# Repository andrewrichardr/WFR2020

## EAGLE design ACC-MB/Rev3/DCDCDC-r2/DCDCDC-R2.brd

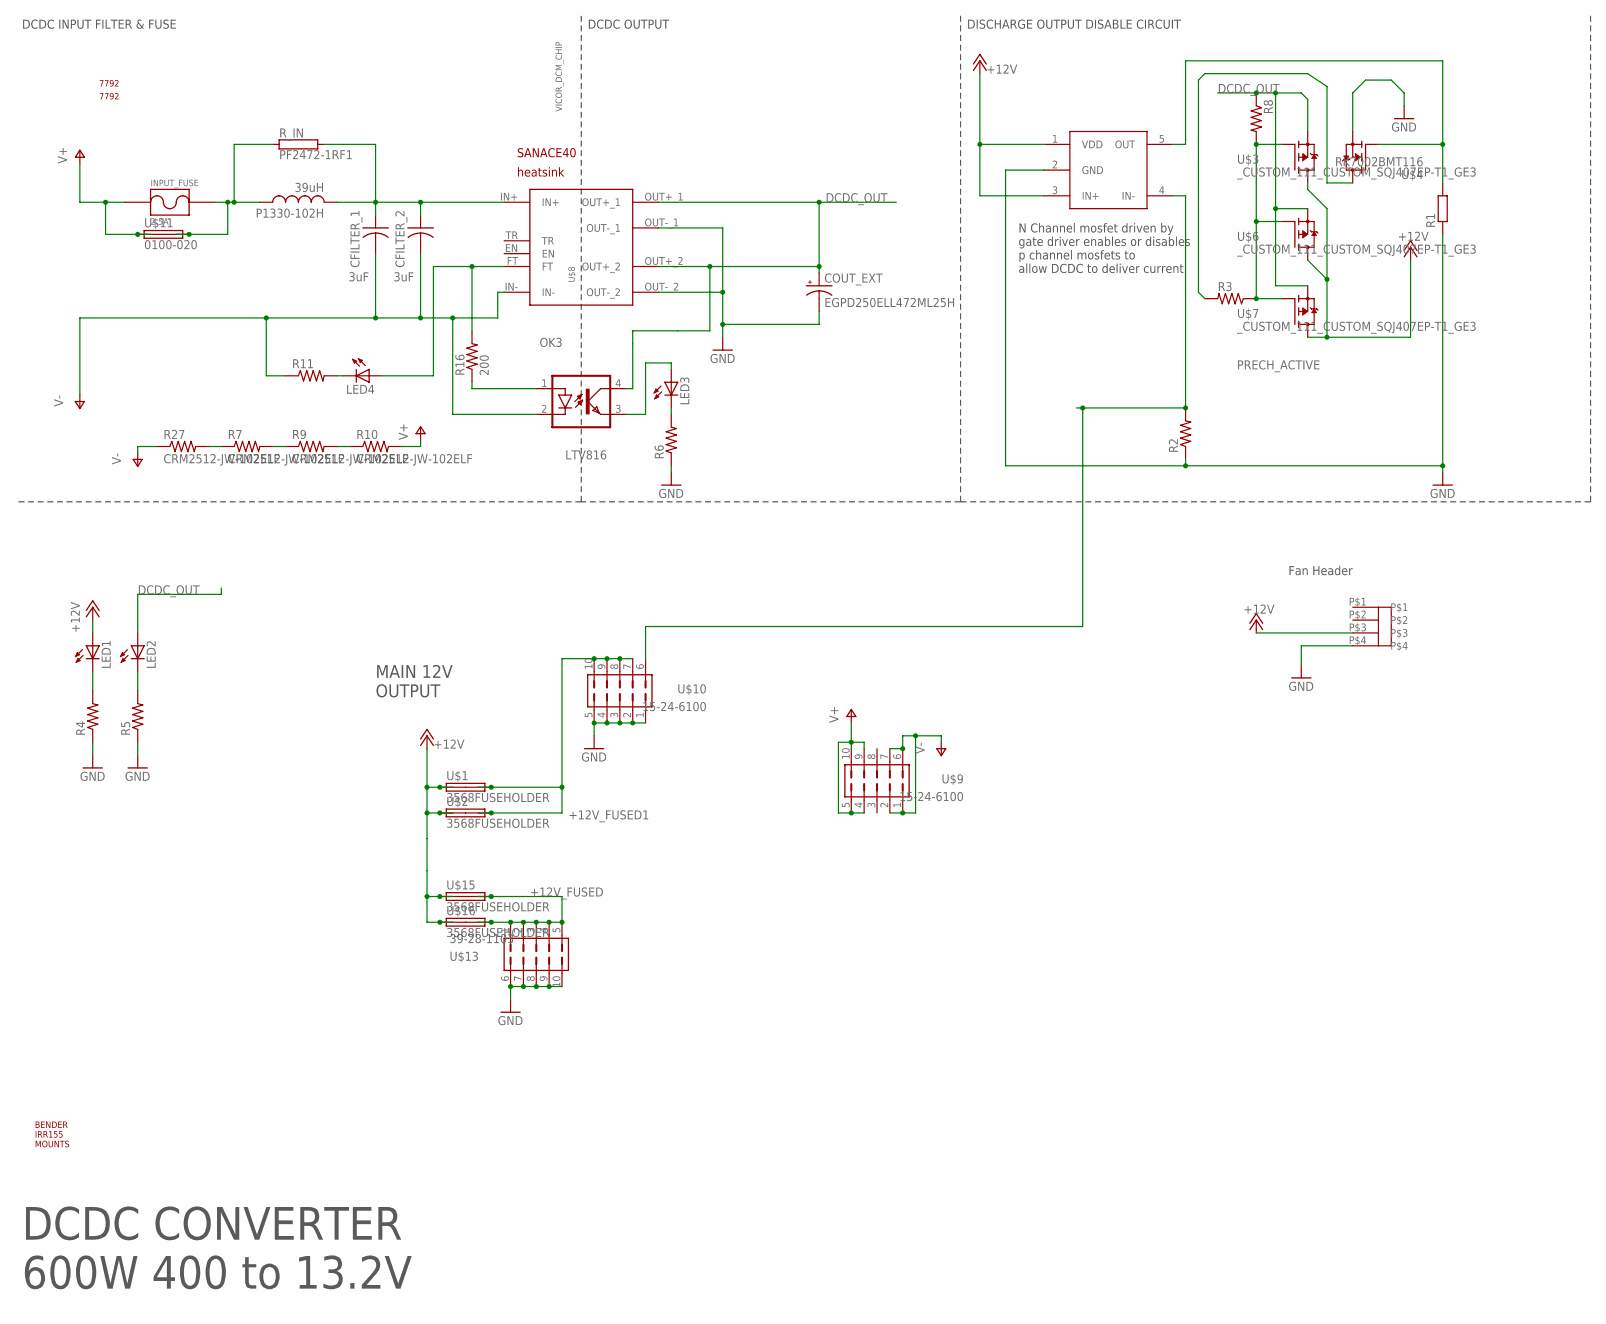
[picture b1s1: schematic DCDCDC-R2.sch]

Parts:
CFILTER_1, CFILTER_2: 3uF; CERALINK_FA3
COUT_EXT: EGPD250ELL472ML25H; E7,5-16
INPUT_FUSE: 2.5A; _CUSTOM_PARTS_LF_885
LED1, LED2, LED3, LED4: LEDCHIPLED_0805; CHIPLED_0805
OK3: LTV816; DIL04
P1330-102H: 39uH; L_1510_NONSTANDARD
R1: R-EU_R0805; R0805
R2, R3, R4, R5, R6, R8, R11: R-US_R0805; R0805
R7, R9, R10, R27: CRM2512-JW-102ELF; R2512
R16: 200; R2010
R_IN: PF2472-1RF1; TO-247-2V
U$1, U$2, U$15, U$16: 3568FUSEHOLDER; 3568
U$3, U$6, U$7: _CUSTOM_111_CUSTOM_SQJ407EP-T1_GE3; _CUSTOM_111_CUSTOM_TRANS_SIRA90DP-T1-GE3
U$4: RK7002BMT116; SOT23
U$5: UCC27511AQDBVRQ1; SOT23-5L
U$8: VICOR_DCM_CHIP; VICOR_CHIP_HEATSINK
U$9, U$10: 15-24-6100
U$11: 0100-020
U$12: VICOR_HEATSINK_DOUBLE
U$13: 39-28-1103
U$14, U$17: 7792
U$18: 9GAX0412P3S0031; SANACE40
U$19: 470531000
U$20: BENDER_IRR155

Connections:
+12V: LED1.A, U$1.L1 (1A), U$1.L2 (1B), U$2.L1 (1A), U$2.L2 (1B), U$3.5 (D), U$5.1 (VDD), U$5.3 (IN+), U$6.5 (D), U$7.5 (D), U$15.L1 (1A), U$15.L2 (1B), U$16.L1 (1A), U$16.L2 (1B), U$19.P$3
+12V_FUSED: U$13.1, U$13.2, U$13.3, U$13.4, U$13.5, U$15.R1 (2A), U$15.R2 (2B), U$16.R1 (2A), U$16.R2 (2B)
+12V_FUSED1: U$1.R1 (2A), U$1.R2 (2B), U$2.R1 (2A), U$2.R2 (2B), U$10.7, U$10.8, U$10.9, U$10.10
DCDC_OUT: COUT_EXT.+, LED2.A, OK3.4 (COL), R8.1, U$3.1 (S), U$3.2 (S), U$3.3 (S), U$6.1 (S), U$6.2 (S), U$6.3 (S), U$7.1 (S), U$7.2 (S), U$7.3 (S), U$8.OUT+_1, U$8.OUT+_2
GND: COUT_EXT.-, R1.1, R2.1, R4.1, R5.1, R6.1, U$4.2 (S), U$5.2 (GND), U$8.OUT-_1, U$8.OUT-_2, U$10.1, U$10.2, U$10.3, U$10.4, U$10.5, U$13.6, U$13.7, U$13.8, U$13.9, U$13.10, U$19.P$4
unnamed: R3.1, R8.2, U$3.4 (G), U$6.4 (G), U$7.4 (G)
unnamed: R1.2, U$4.1 (G), U$5.5 (OUT)
unnamed: CFILTER_1.P$1 (1), CFILTER_2.P$1 (1), P1330-102H.P$2 (2), R_IN.2, U$8.IN+
unnamed: R3.2, U$4.3 (D)
unnamed: LED1.C, R4.2
unnamed: LED2.C, R5.2
unnamed: LED4.A, R16.2, U$8.FT
unnamed: OK3.1 (A), R16.1
unnamed: LED3.C, R6.2
unnamed: LED3.A, OK3.3 (EMIT)
unnamed: LED4.C, R11.2
unnamed: R7.1, R27.2
unnamed: R7.2, R9.1
unnamed: R9.2, R10.1
PRECH_ACTIVE: R2.2, U$5.4 (IN-), U$10.6
V+: INPUT_FUSE.P$1, R10.2, U$9.4, U$9.5, U$9.9, U$9.10, U$11.P$1 (1A), U$11.P$3 (1B)
V+_FUSED: INPUT_FUSE.P$2, P1330-102H.P$1 (1), R_IN.1, U$11.P$2 (2A), U$11.P$4 (2B)
V-: CFILTER_1.P$2 (2), CFILTER_2.P$2 (2), OK3.2 (C), R11.1, R27.1, U$8.IN-, U$9.1, U$9.2, U$9.6, U$9.7

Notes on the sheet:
DCDC CONVERTER 600W 400 to 13.2V
DISCHARGE OUTPUT DISABLE CIRCUIT
Fan Header
MAIN 12V OUTPUT
DCDC OUTPUT
DCDC INPUT FILTER & FUSE
N Channel mosfet driven by gate driver enables or disables p channel mosfets to allow DCDC to deliver current

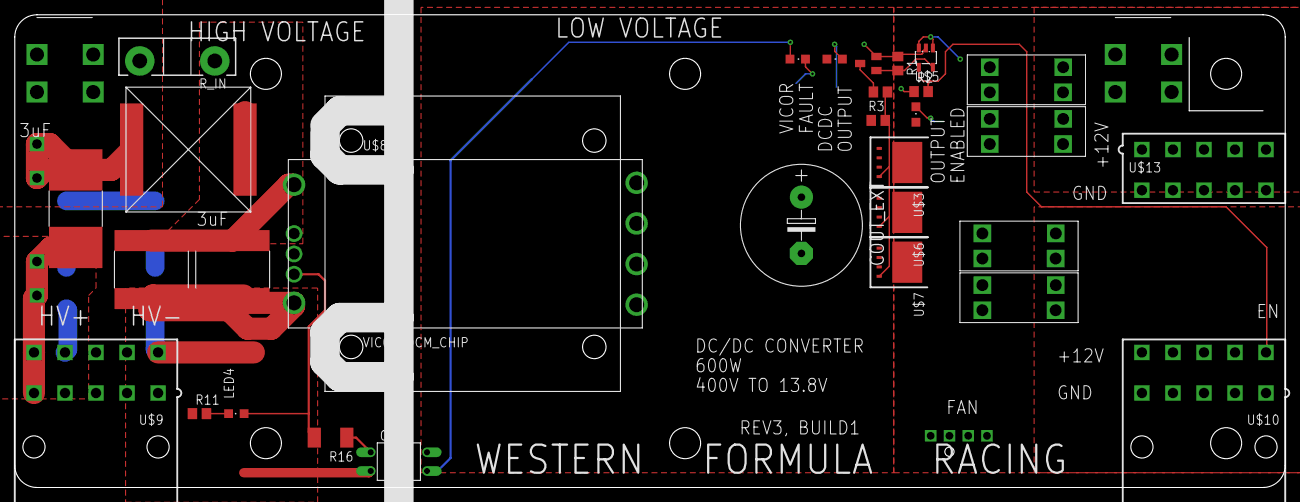
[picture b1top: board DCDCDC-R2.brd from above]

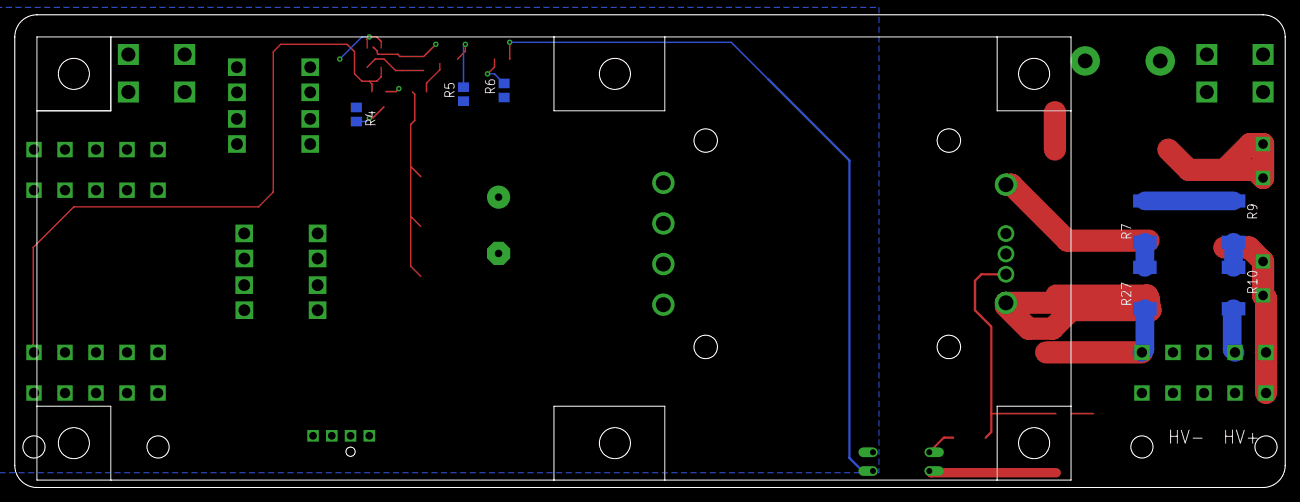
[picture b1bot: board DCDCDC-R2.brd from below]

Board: 2 copper layers, 172.0 x 64.0 mm, 44 parts (8 on the bottom side), 23 nets.

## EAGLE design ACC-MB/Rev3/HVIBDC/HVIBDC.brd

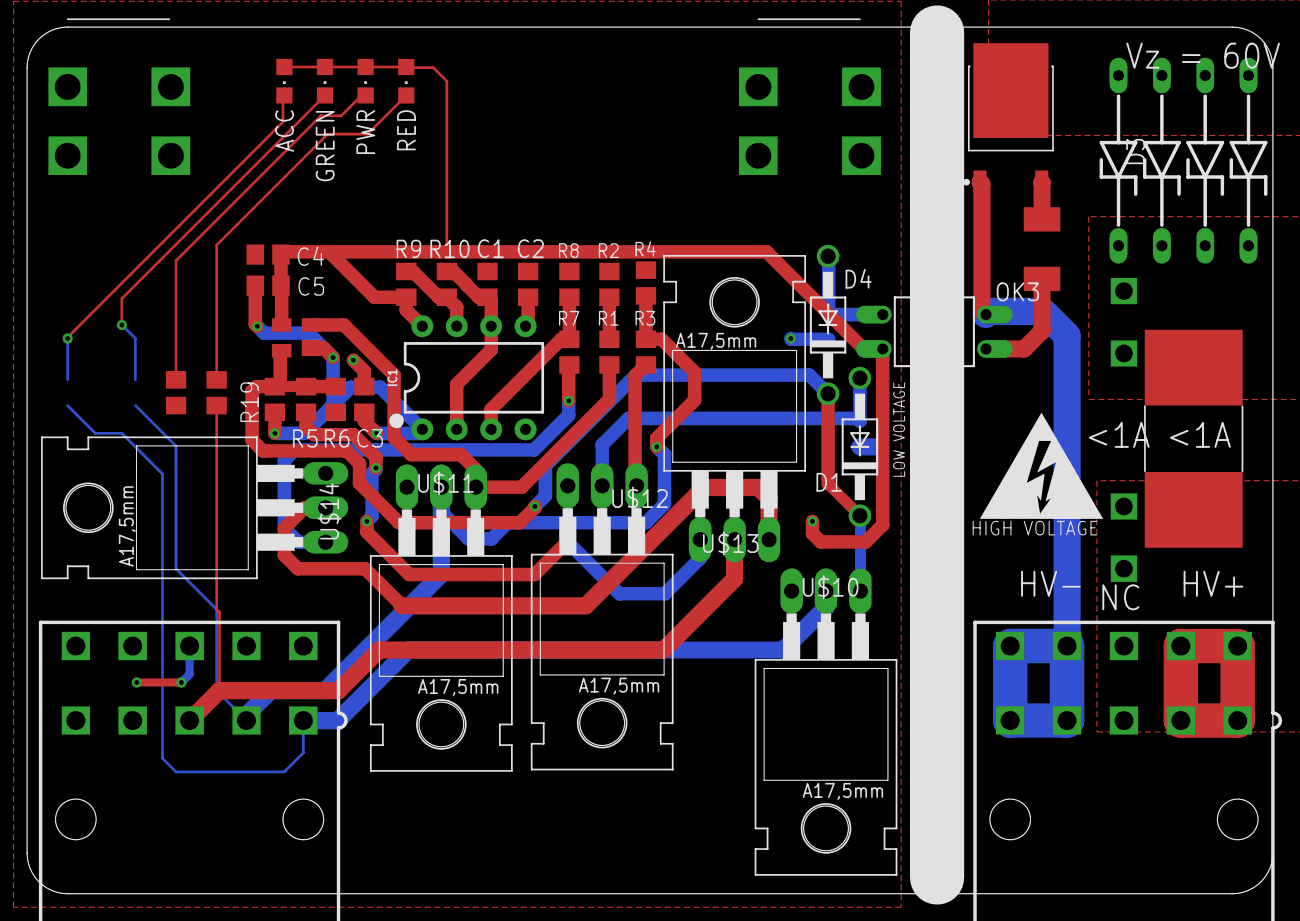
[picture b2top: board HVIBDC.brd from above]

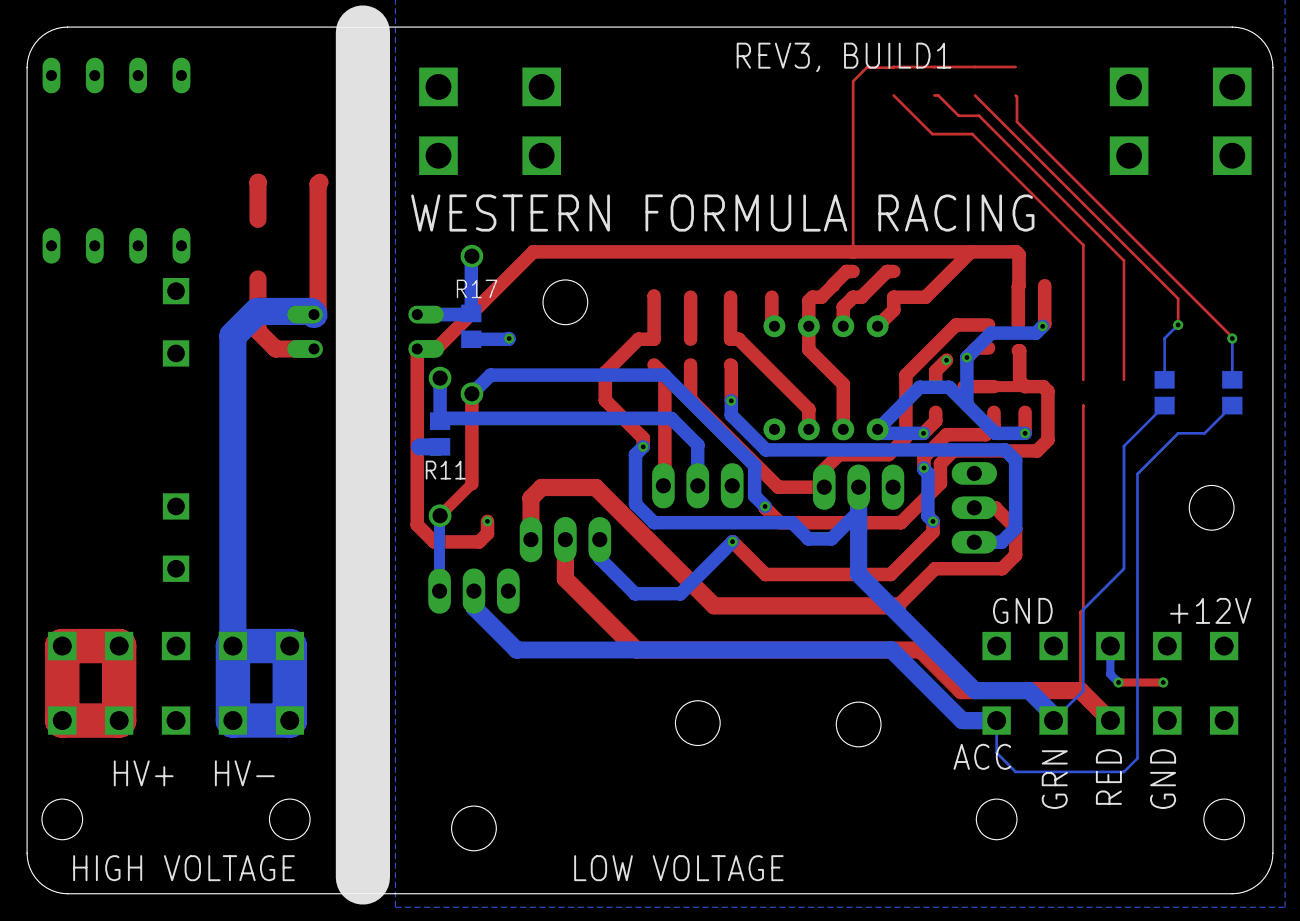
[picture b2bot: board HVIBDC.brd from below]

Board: 2 copper layers, 92.0 x 64.0 mm, 48 parts (4 on the bottom side), 28 nets.

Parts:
ACC: CHIPLED_0805
C1: 39n; C0805
C2: 10n; C0805
C3: 100n; C0805
C4: 4.7u; C0805
C5: 0.1u; C0805
D1, D4: 1N4004; DO41-10
D2, D3, D5, D6: 1N4758A - 56Vz; ZDIO12.5
GREEN: CHIPLED_0805
HV+_FUSE_DRY: _CUSTOM_PARTS_LF_885
IC1: 555; DIP08
LEDR1, LEDR2, LEDR3, LEDR4: R0805
OK3: LTV816; DIL04
PWR: CHIPLED_0805
R1, R3, R5, R7: 100; R0805
R2, R4, R6, R8, R11: 1M; R0805
R9: 2.2k; R0805
R10: 4.7M; R0805
R16: 200; R2010
R17, R19: 10k; R0805
RED: CHIPLED_0805
U$1, U$2: 15-24-6100
U$3, U$4: 7792
U$8: 0100-020
U$10, U$11, U$12, U$13, U$14: BUZ11; TO220
U$15: MIC4417; PDM_2019_REVB_MIC4416YM4-TR
U$22: _CUSTOM_IXCY10M90SD2PAK; TO228P991X238-3

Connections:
+12V: ACC.A, C3.1, C4.1, C5.1, GREEN.A, IC1.4, IC1.8, OK3.4, PWR.A, R9.2, R11.2, RED.A, U$2.8, U$2.9, U$2.10, U$15.VS
ACC_LGHT: LEDR3.1, U$2.1, U$10.2
AIR_ON: D1.C, D4.C, R5.1, R6.2, R19.2, U$10.1, U$15.CTL
GND: C1.2, C2.2, C3.2, C4.2, C5.2, IC1.1, LEDR4.1, R2.1, R4.1, R6.1, R8.1, R17.1, R19.1, U$2.4, U$2.5, U$2.6, U$2.7, U$10.3, U$11.3, U$12.3, U$14.3, U$15.GND
HV+_DRY_FUSED: D2.C, D3.C, D5.C, D6.C, HV+_FUSE_DRY.P$1, U$8.P$2, U$8.P$4
unnamed: R1.1, R2.2
unnamed: R1.2, U$11.1, U$15.GATE
unnamed: R3.2, U$12.1
unnamed: C2.1, IC1.5
unnamed: IC1.7, R9.1, R10.2
unnamed: R5.2, U$13.1
unnamed: R7.2, U$14.1
unnamed: IC1.3, R7.1, R8.2
unnamed: C1.1, IC1.2, IC1.6, R10.1
unnamed: ACC.C, LEDR3.2
unnamed: GREEN.C, LEDR1.2
unnamed: U$13.3, U$14.2
unnamed: D4.A, OK3.3, R17.2
unnamed: D1.A, R11.1, U$12.2
unnamed: LEDR2.2, RED.C
unnamed: LEDR4.2, PWR.C
unnamed: R16.2, U$22.2
unnamed: D2.A, D3.A, D5.A, D6.A, U$22.3
unnamed: OK3.1, R16.1
TSAL_GRN_GND: LEDR1.1, R3.1, R4.2, U$2.2, U$11.2
TSAL_RED_GND: LEDR2.1, U$2.3, U$13.2
V+: HV+_FUSE_DRY.P$2, U$1.1, U$1.2, U$1.6, U$1.7, U$8.P$1, U$8.P$3
V-: OK3.2, U$1.4, U$1.5, U$1.9, U$1.10, U$22.1

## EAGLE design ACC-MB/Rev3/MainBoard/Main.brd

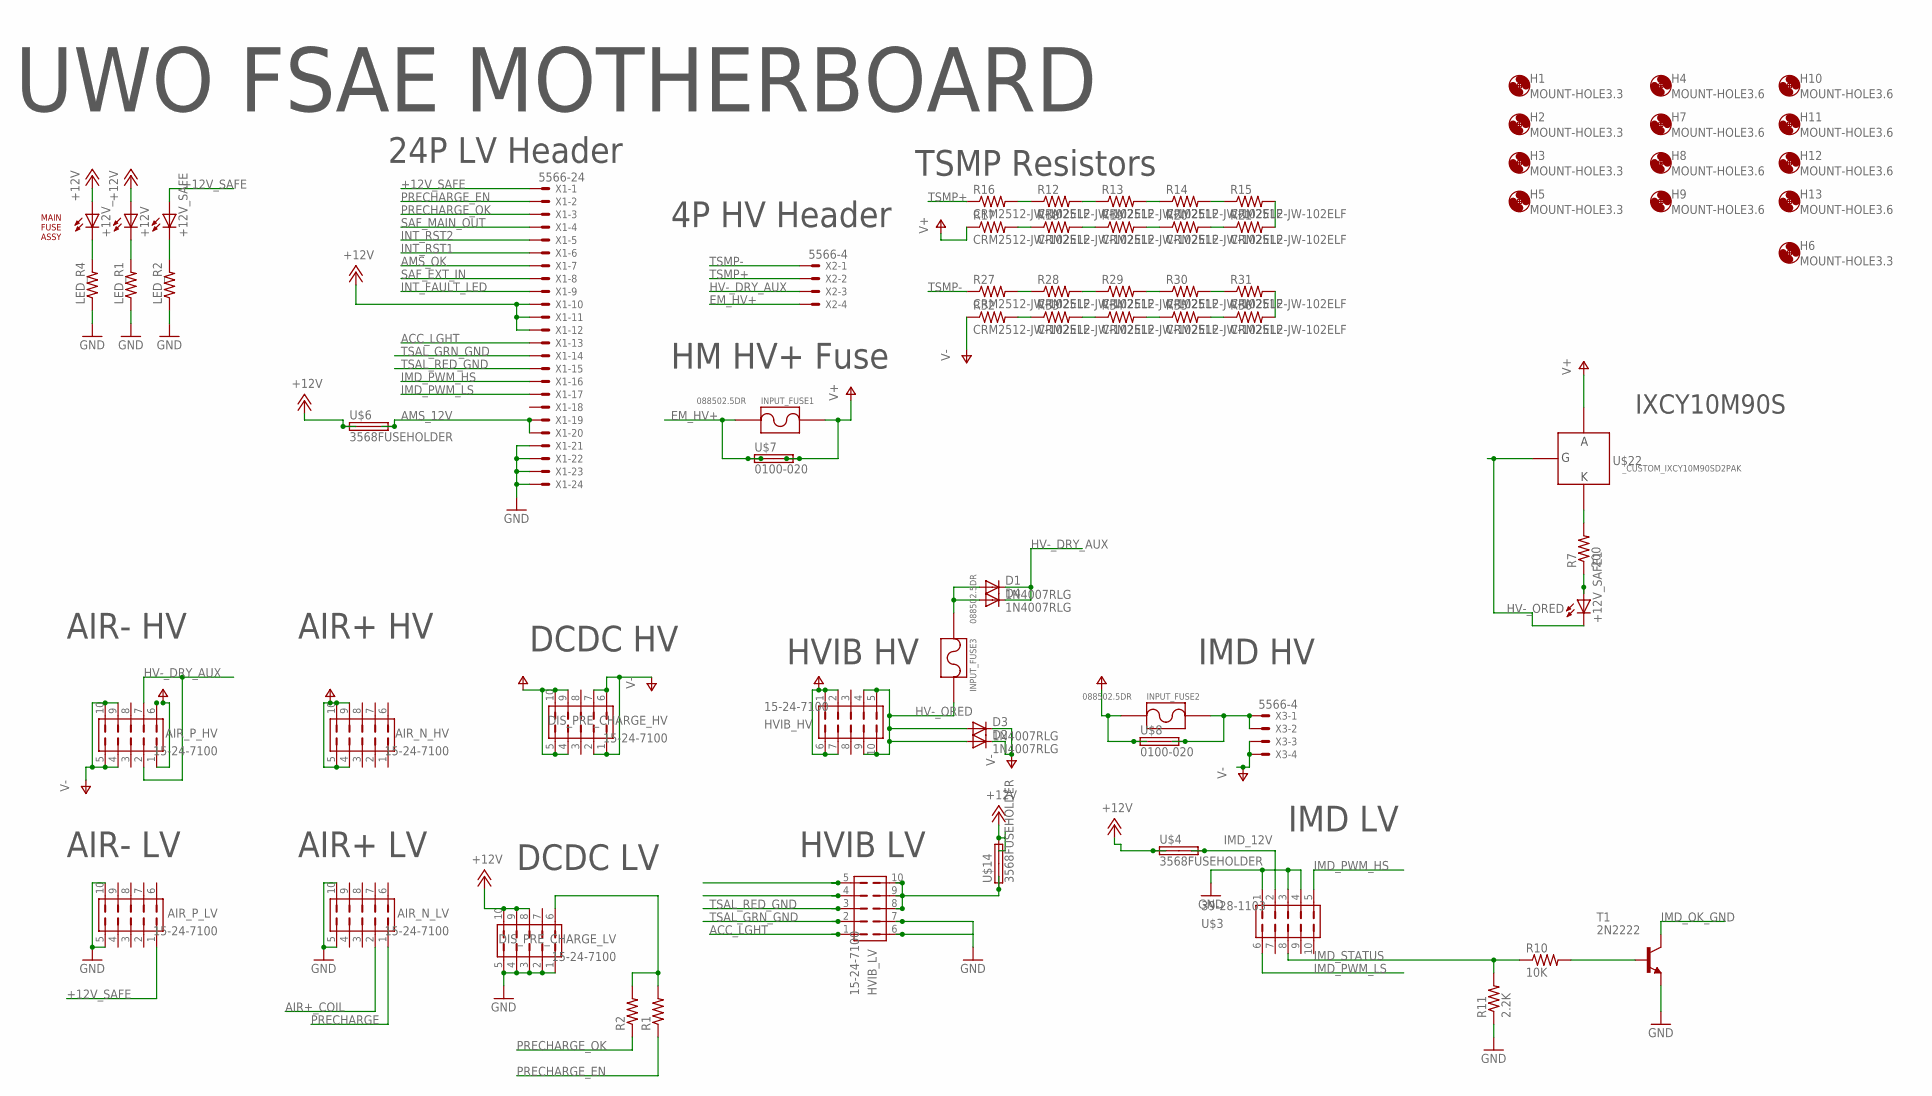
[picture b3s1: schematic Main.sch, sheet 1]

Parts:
+12V, +12V_, +12V_SAFE, +12V_SAFE1: LEDCHIP-LED0805; CHIP-LED0805
AIR_N_HV: 15-24-7100; 5566-10-BMI
AIR_N_LV: 15-24-7100; 5566-10-BMI
AIR_P_HV: 15-24-7100; 5566-10-BMI
AIR_P_LV: 15-24-7100; 5566-10-BMI
D1, D2, D3, D4: 1N4007RLG; DO41-10
DIS_PRE_CHARGE_HV: 15-24-7100; 5566-10-BMI
DIS_PRE_CHARGE_LV: 15-24-7100; 5566-10-BMI
H1, H2, H3, H5, H6: MOUNT-HOLE3.3; 3,3
H4, H7, H8, H9, H10, H11, H12, H13: MOUNT-HOLE3.6; 3,6
HVIB_HV: 15-24-7100; 5566-10-BMI
HVIB_LV: 15-24-7100; 5566-10-BMI
INPUT_FUSE1, INPUT_FUSE2, INPUT_FUSE3: 088502.5DR; _CUSTOM_PARTS_LF_885
LED_R1, LED_R2, LED_R4: R-US_R0805; R0805
R1, R2: R-US_R0805; R0805
R7: 200; R2010
R10: 10K; M0805
R11: 2.2K; M0805
R12, R13, R14, R15, R16, R17, R18, R19, R20, R21, R27, R28, R29, R30, R31, R32, R33, R34, R35, R36: CRM2512-JW-102ELF; R2512
T1: 2N2222; TO92-EBC-OVAL
U$1: MAINFUSEASSY
U$3: 39-28-1103
U$4, U$6, U$14: 3568FUSEHOLDER; 3568
U$7, U$8: 0100-020
U$22: _CUSTOM_IXCY10M90SD2PAK; TO228P991X238-3
X1: 5566-24
X2, X3: 5566-4

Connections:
+12V: +12V.A, +12V_.A, DIS_PRE_CHARGE_LV.8, DIS_PRE_CHARGE_LV.9, DIS_PRE_CHARGE_LV.10, U$4.L1 (1A), U$4.L2 (1B), U$6.L1 (1A), U$6.L2 (1B), U$14.R1 (2A), U$14.R2 (2B), X1.10, X1.11, X1.12; also elsewhere on the board
+12V_SAFE: +12V_SAFE.A, AIR_P_LV.1, X1.1; also elsewhere on the board
ACC_LGHT: HVIB_LV.1, X1.13
AIR+_COIL: AIR_N_LV.2; also elsewhere on the board
AMS_12V: U$6.R1 (2A), U$6.R2 (2B), X1.19, X1.20
AMS_OK: X1.7; also elsewhere on the board
EM_HV+: INPUT_FUSE1.P$1, U$7.P$1 (1A), U$7.P$3 (1B), X2.4
GND: AIR_N_LV.5, AIR_N_LV.10, AIR_P_LV.5, AIR_P_LV.10, DIS_PRE_CHARGE_LV.1, DIS_PRE_CHARGE_LV.2, DIS_PRE_CHARGE_LV.3, DIS_PRE_CHARGE_LV.4, DIS_PRE_CHARGE_LV.5, HVIB_LV.7, LED_R1.1, LED_R2.1, LED_R4.1, R11.1, T1.E, U$3.1, U$3.3, U$3.4, X1.21, X1.22, X1.23, X1.24; also elsewhere on the board
HV-_DRY_AUX: AIR_P_HV.2, AIR_P_HV.7, D1.C, D4.C, X2.3
HV-_ORED: +12V_SAFE1.C, D2.A, D3.A, HVIB_HV.4, HVIB_HV.5, HVIB_HV.9, HVIB_HV.10, INPUT_FUSE3.P$2, U$22.1 (G)
IMD_12V: U$3.2, U$4.R1 (2A), U$4.R2 (2B)
IMD_OK_GND: T1.C; also elsewhere on the board
IMD_PWM_HS: U$3.5, X1.16
IMD_PWM_LS: U$3.6, X1.17
IMD_STATUS: R10.1, R11.2, U$3.8
INT_FAULT_LED: X1.9; also elsewhere on the board
INT_RST1: X1.6; also elsewhere on the board
INT_RST2: X1.5; also elsewhere on the board
unnamed: +12V.C, LED_R1.2
unnamed: R10.2, T1.B
unnamed: +12V_.C, LED_R4.2
unnamed: +12V_SAFE.C, LED_R2.2
unnamed: R12.1, R16.2
unnamed: R12.2, R13.1
unnamed: R13.2, R14.1
unnamed: R14.2, R15.1
unnamed: R15.2, R21.2
unnamed: R20.2, R21.1
unnamed: R19.2, R20.1
unnamed: R18.2, R19.1
unnamed: R17.2, R18.1
unnamed: DIS_PRE_CHARGE_LV.6, R1.2, R2.2
unnamed: INPUT_FUSE2.P$2, U$8.P$2 (2A), U$8.P$4 (2B), X3.1, X3.2
unnamed: R7.2, U$22.2 (K)
unnamed: R27.2, R28.1
unnamed: R28.2, R29.1
unnamed: R29.2, R30.1
unnamed: R30.2, R31.1
unnamed: R31.2, R36.2
unnamed: R35.2, R36.1
unnamed: R34.2, R35.1
unnamed: R33.2, R34.1
unnamed: R32.2, R33.1
unnamed: +12V_SAFE1.A, R7.1
unnamed: HVIB_LV.8, HVIB_LV.9, HVIB_LV.10, U$14.L1 (1A), U$14.L2 (1B)
unnamed: D1.A, D4.A, INPUT_FUSE3.P$1
PRECHARGE: AIR_N_LV.1; also elsewhere on the board
PRECHARGE_EN: R1.1, X1.2; also elsewhere on the board
PRECHARGE_OK: R2.1, X1.3; also elsewhere on the board
SAF_EXT_IN: X1.8; also elsewhere on the board
SAF_MAIN_OUT: X1.4; also elsewhere on the board
TSAL_GRN_GND: HVIB_LV.2, X1.14
TSAL_RED_GND: HVIB_LV.3, X1.15
TSMP+: R16.1, X2.2
TSMP-: R27.1, X2.1
V+: AIR_N_HV.4, AIR_N_HV.5, AIR_N_HV.9, AIR_N_HV.10, AIR_P_HV.1, AIR_P_HV.6, DIS_PRE_CHARGE_HV.4, DIS_PRE_CHARGE_HV.5, DIS_PRE_CHARGE_HV.9, DIS_PRE_CHARGE_HV.10, HVIB_HV.1, HVIB_HV.2, HVIB_HV.6, HVIB_HV.7, INPUT_FUSE1.P$2, INPUT_FUSE2.P$1, R17.1, U$7.P$2 (2A), U$7.P$4 (2B), U$8.P$1 (1A), U$8.P$3 (1B), U$22.3 (A)
V-: AIR_P_HV.4, AIR_P_HV.5, AIR_P_HV.9, AIR_P_HV.10, D2.C, D3.C, DIS_PRE_CHARGE_HV.1, DIS_PRE_CHARGE_HV.2, DIS_PRE_CHARGE_HV.6, DIS_PRE_CHARGE_HV.7, R32.1, X3.3, X3.4

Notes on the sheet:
UWO FSAE MOTHERBOARD
TSMP Resistors
24P LV Header
4P HV Header
HM HV+ Fuse
AIR- HV
AIR- LV
AIR+ LV
AIR+ HV
DCDC HV
DCDC LV
HVIB HV
HVIB LV
IMD HV
IMD LV
IXCY10M90S

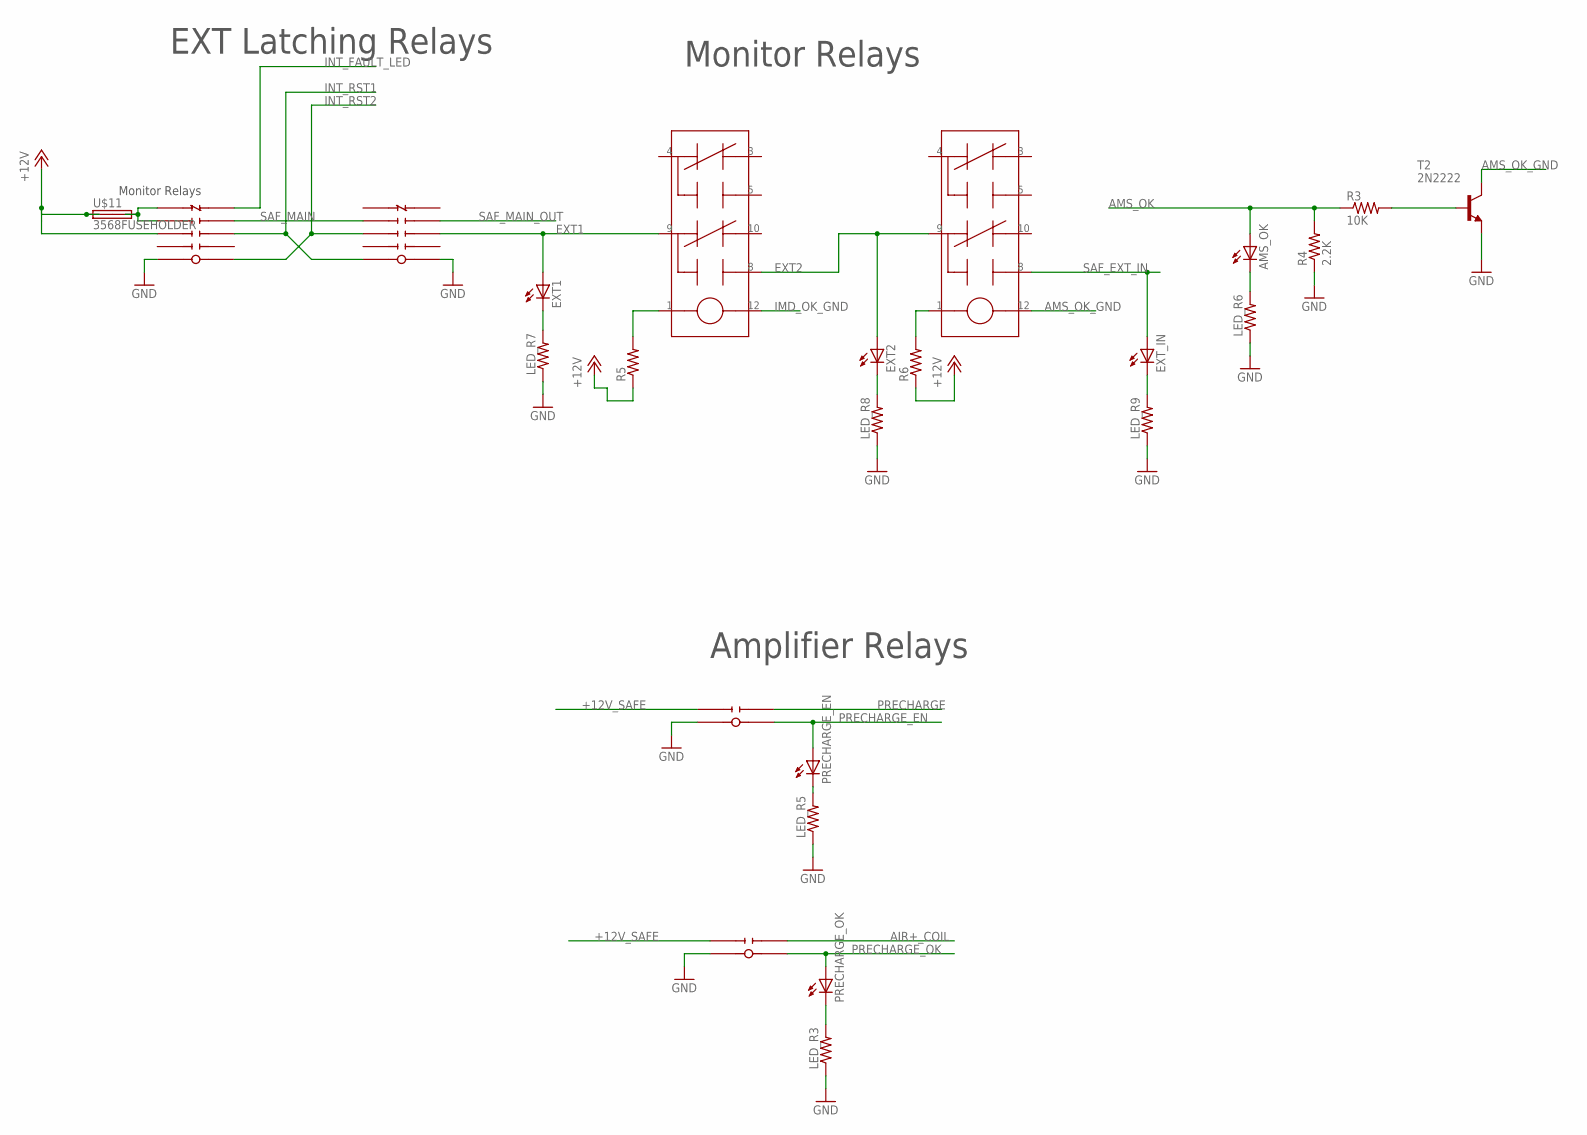
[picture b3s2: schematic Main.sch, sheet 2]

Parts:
AMS_OK: LEDCHIP-LED0805; CHIP-LED0805
EXT1, EXT2: LEDCHIP-LED0805; CHIP-LED0805
EXT_IN: LEDCHIP-LED0805; CHIP-LED0805
LED_R3, LED_R5, LED_R6, LED_R7, LED_R8, LED_R9: R-US_R0805; R0805
PRECHARGE_EN: LEDCHIP-LED0805; CHIP-LED0805
PRECHARGE_OK: LEDCHIP-LED0805; CHIP-LED0805
R3: 10K; M0805
R4: 2.2K; M0805
R5, R6: R-US_R0805; R0805
T2: 2N2222; TO92-EBC-OVAL
U$2, U$5: SR4M4012_TE; SR4M4012_FOOT
U$9, U$10: G5NB-1A-E
U$11: 3568FUSEHOLDER; 3568
U$12, U$13: V23079B1203B301

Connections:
+12V: R5.1, R6.1, U$2.NOA2, U$11.L1 (1A), U$11.L2 (1B); also elsewhere on the board
+12V_SAFE: U$9.2 (NOA1), U$10.2 (NOA1); also elsewhere on the board
AIR+_COIL: U$9.3 (NOB1); also elsewhere on the board
AMS_OK: AMS_OK.A, R3.1, R4.2; also elsewhere on the board
AMS_OK_GND: T2.C, U$13.12
EXT1: EXT1.A, U$5.NOB2, U$12.9
EXT2: EXT2.A, U$12.8, U$13.9
GND: LED_R3.1, LED_R5.1, LED_R6.1, LED_R7.1, LED_R8.1, LED_R9.1, R4.1, T2.E, U$2.COIL+, U$5.COIL-, U$9.1 (COIL+), U$10.1 (COIL+); also elsewhere on the board
IMD_OK_GND: U$12.12; also elsewhere on the board
INT_FAULT_LED: U$2.NCB4; also elsewhere on the board
INT_RST1: U$2.NOB2, U$5.COIL+; also elsewhere on the board
INT_RST2: U$2.COIL-, U$5.NOA2; also elsewhere on the board
unnamed: U$2.NCA4, U$2.NOA3, U$11.R1 (2A), U$11.R2 (2B)
unnamed: LED_R5.2, PRECHARGE_EN.C
unnamed: LED_R3.2, PRECHARGE_OK.C
unnamed: AMS_OK.C, LED_R6.2
unnamed: EXT1.C, LED_R7.2
unnamed: EXT2.C, LED_R8.2
unnamed: EXT_IN.C, LED_R9.2
unnamed: R3.2, T2.B
unnamed: R5.2, U$12.1
unnamed: R6.2, U$13.1
PRECHARGE: U$10.3 (NOB1); also elsewhere on the board
PRECHARGE_EN: PRECHARGE_EN.A, U$10.4 (COIL-); also elsewhere on the board
PRECHARGE_OK: PRECHARGE_OK.A, U$9.4 (COIL-); also elsewhere on the board
SAF_EXT_IN: EXT_IN.A, U$13.8; also elsewhere on the board
SAF_MAIN: U$2.NOB3, U$5.NOA3
SAF_MAIN_OUT: U$5.NOB3; also elsewhere on the board

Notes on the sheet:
Monitor Relays
EXT Latching Relays
Amplifier Relays

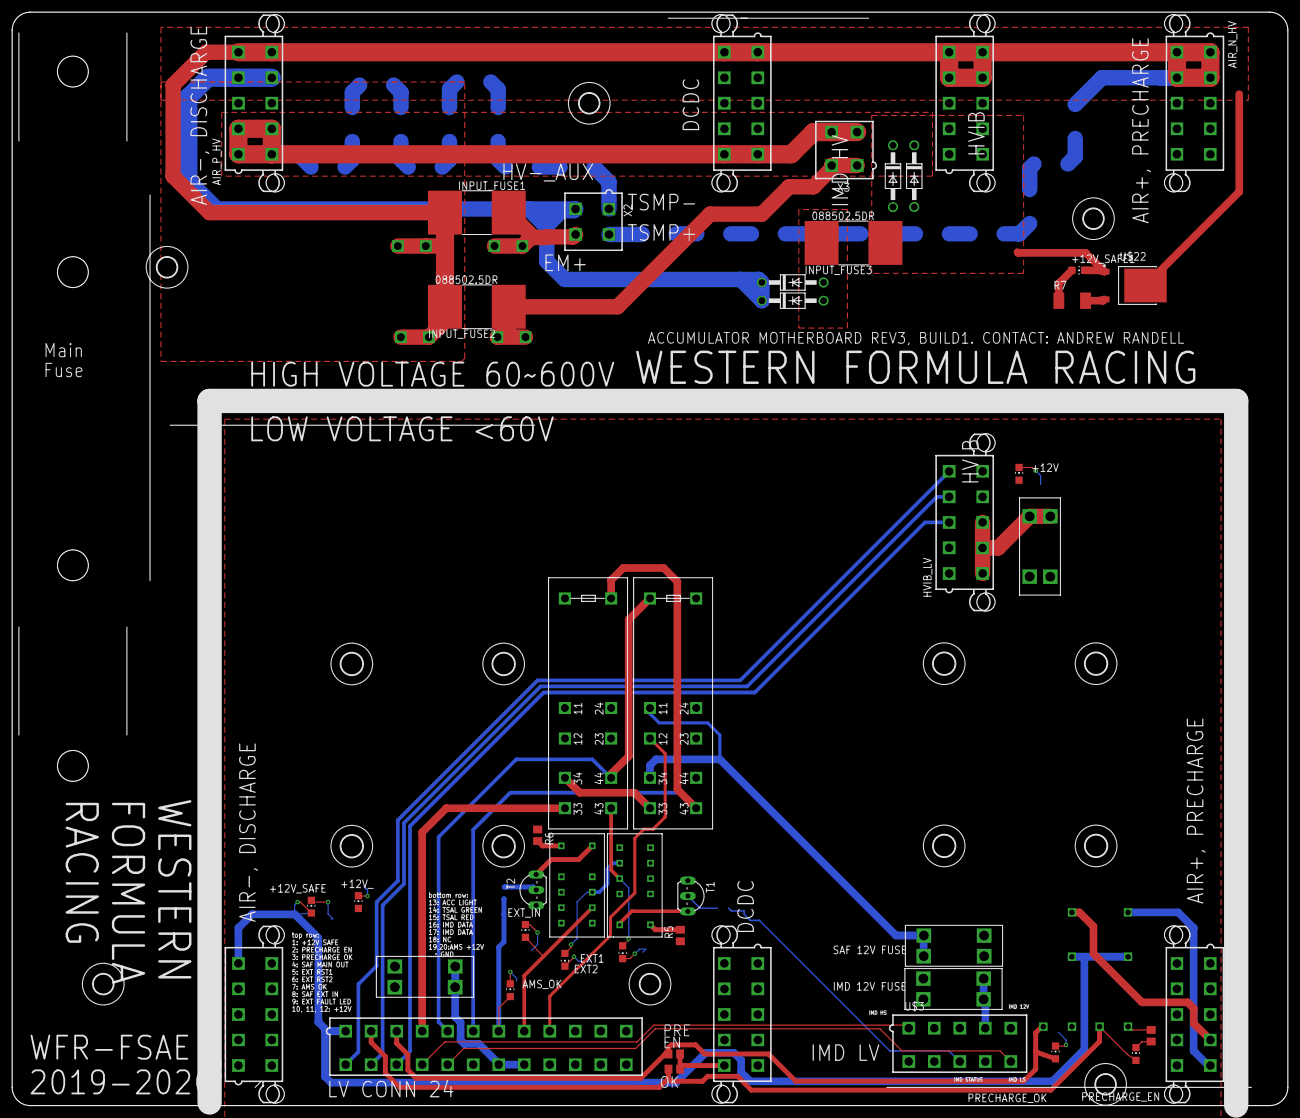
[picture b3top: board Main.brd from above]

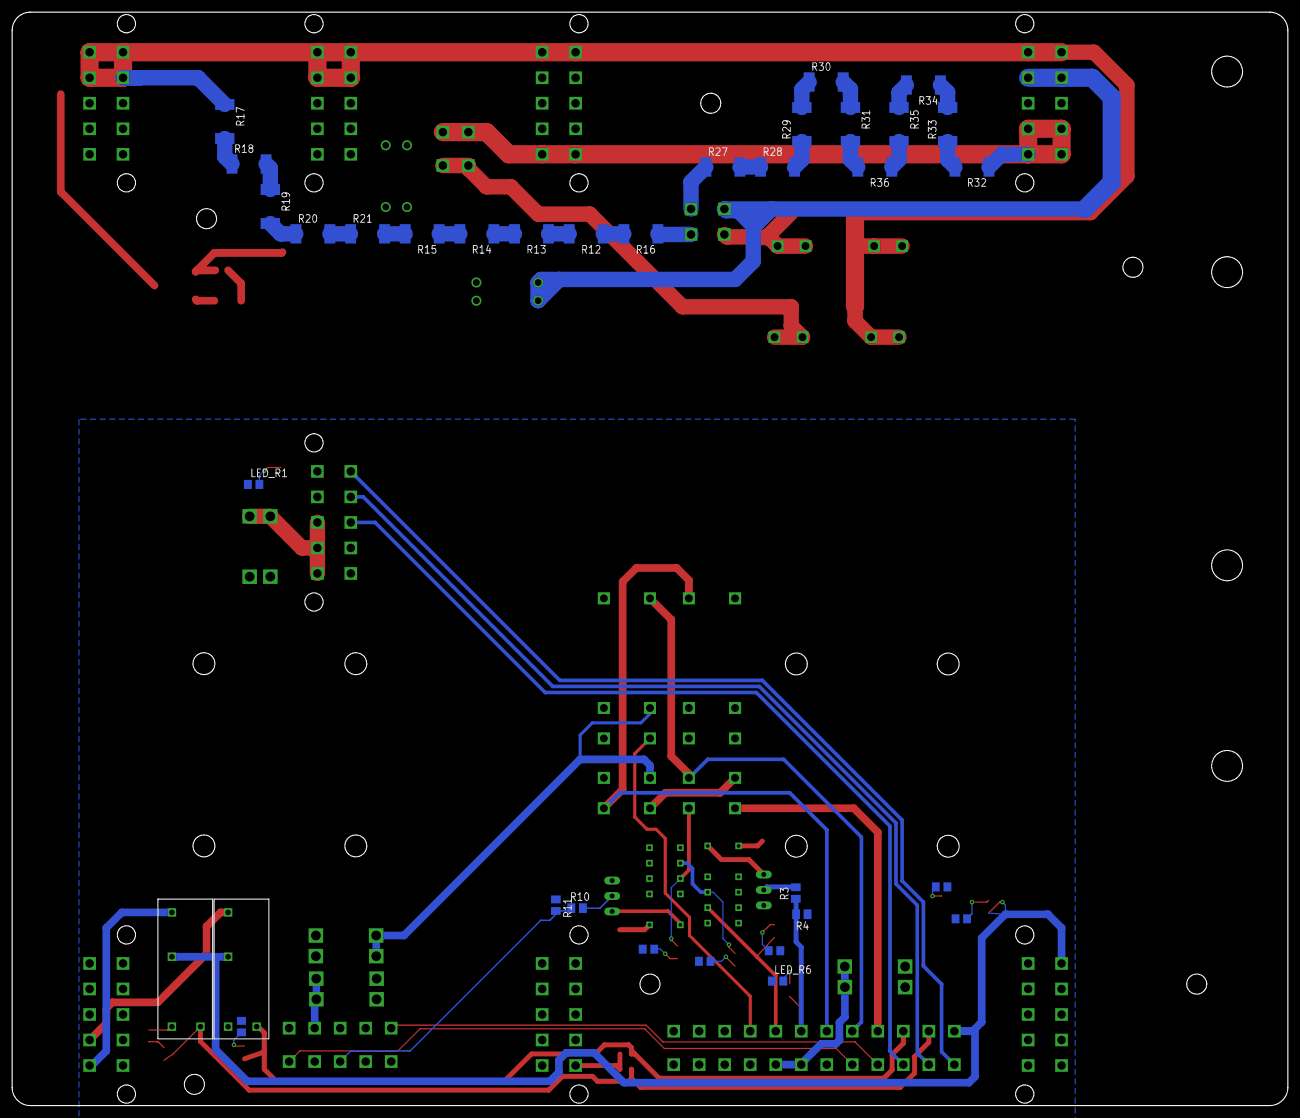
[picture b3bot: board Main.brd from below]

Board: 2 copper layers, 210.0 x 180.0 mm, 97 parts (34 on the bottom side), 71 nets.

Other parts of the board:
H14: MOUNT-HOLE3.3; 3,3

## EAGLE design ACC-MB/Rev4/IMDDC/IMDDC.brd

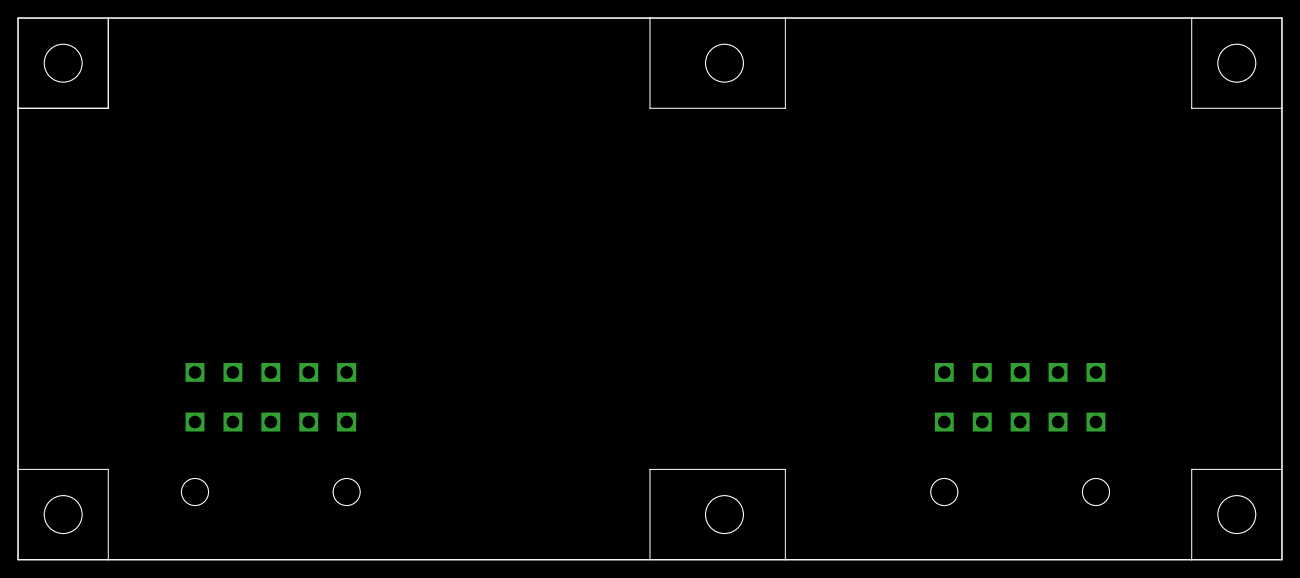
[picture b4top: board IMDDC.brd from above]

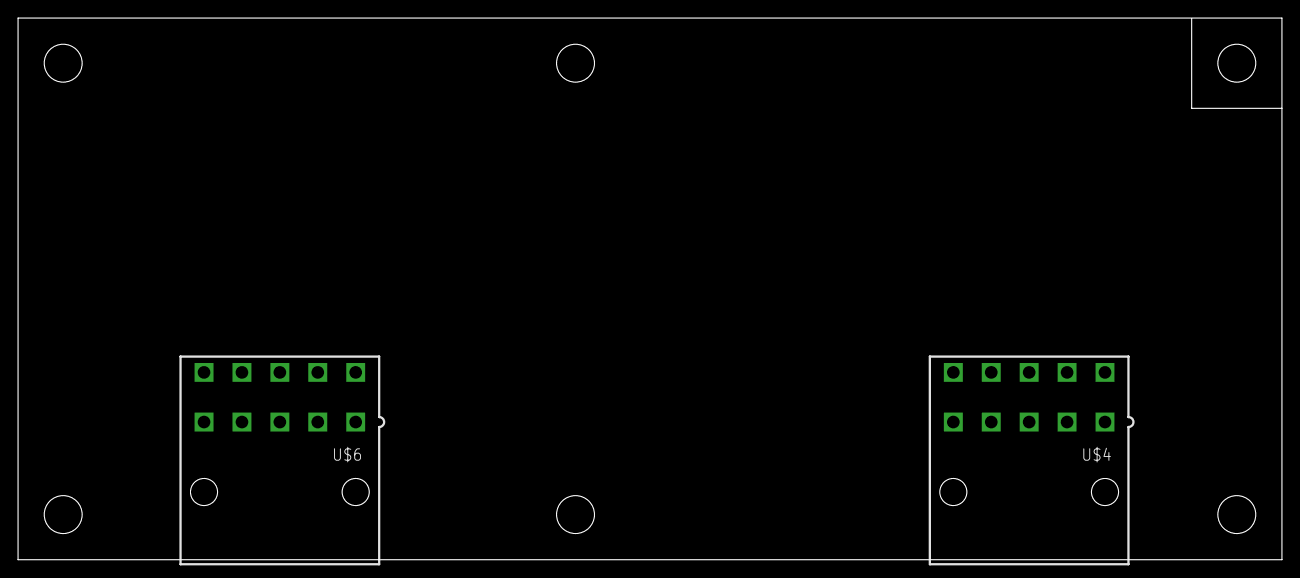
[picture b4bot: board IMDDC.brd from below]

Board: 2 copper layers, 140.0 x 60.0 mm, 3 parts (2 on the bottom side), 5 nets, no tracks yet.

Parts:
U$1: BENDER_IRR155
U$4, U$6: 15-24-6100

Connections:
+12V: U$6.9, U$6.10
GND: U$6.4, U$6.5
HV+_DRY: U$4.1, U$4.6
HV+_WET: U$4.3, U$4.8
HV-_DRY: U$4.5, U$4.10

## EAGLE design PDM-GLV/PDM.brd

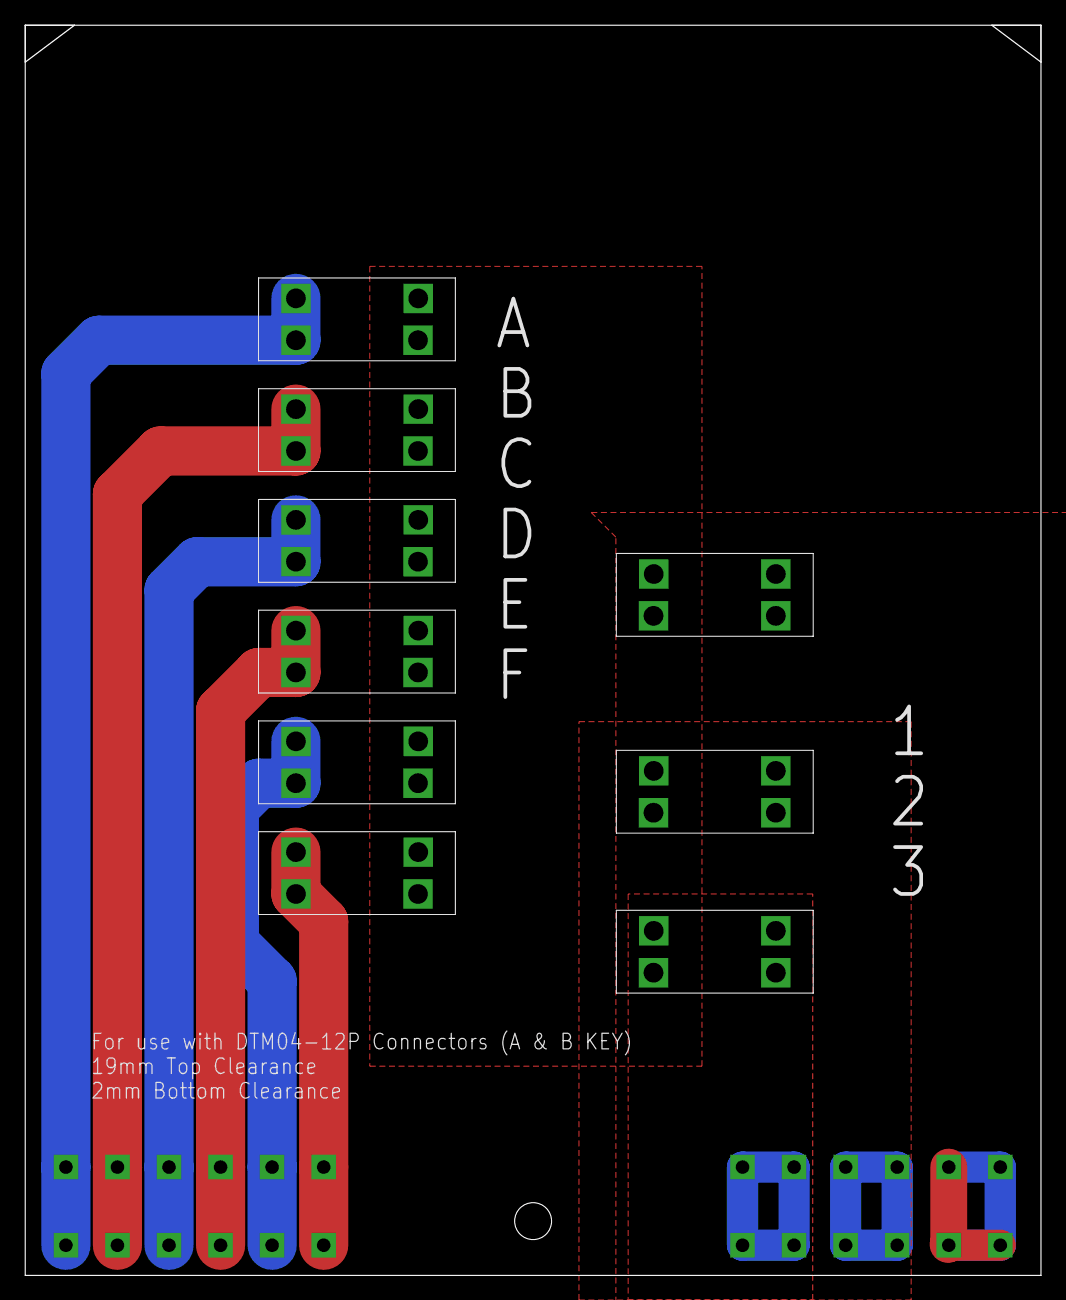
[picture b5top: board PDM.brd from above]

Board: 2 copper layers, 82.5 x 101.6 mm, 10 parts (0 on the bottom side), 10 nets.

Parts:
CH1, CH2, CH3, CH4, CH5, CH6, CH7, CH9, CH11: 3568FUSEHOLDER; 3568
U$4: DTM1312PA12BR008; DE_12X2_PIN_HEADER

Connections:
CH1: CH1.L1, CH1.L2, U$4.6B, U$4.7B
CH2: CH2.L1, CH2.L2, U$4.5B, U$4.8B
CH3: CH3.L1, CH3.L2, U$4.4B, U$4.9B
CH4: CH4.L1, CH4.L2, U$4.3B, U$4.10B
CH5: CH5.L1, CH5.L2, U$4.2B, U$4.11B
CH6: CH6.L1, CH6.L2, U$4.1B, U$4.12B
CH8: CH7.L1, CH7.L2, U$4.5A, U$4.6A, U$4.7A, U$4.8A
CH10: CH9.L1, CH9.L2, U$4.3A, U$4.4A, U$4.9A, U$4.10A
CH11: CH11.L1, CH11.L2, U$4.1A, U$4.2A, U$4.11A, U$4.12A
COMMON: CH1.R1, CH1.R2, CH2.R1, CH2.R2, CH3.R1, CH3.R2, CH4.R1, CH4.R2, CH5.R1, CH5.R2, CH6.R1, CH6.R2, CH7.R1, CH7.R2, CH9.R1, CH9.R2, CH11.R1, CH11.R2

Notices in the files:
parts and their libraries:
SparkFun-IC-Special-Function: Licensing: Creative Commons ShareAlike 4.0 International - https://creativecommons.org/licenses/by-sa/4.0
